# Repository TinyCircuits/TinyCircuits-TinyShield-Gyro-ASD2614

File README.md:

# TinyCircuits TinyShield Gyro Board
# ASD2614 Rev1

These design files are located under design_files/ for the TinyCircuits ASD2614 Rev 1 PCB.  This is a TinyShield board (Square Version, 20mm x 20mm, or Circular 20mm diameter) that has a ST L3G4200D Gyroscope, local power supply and level shifters to connect between the TinyDuino and the accelerometer. 

Format is in Cadsoft Eagle format - Eagle version 6.2 was used for the original design.

For more infomation on this, check out the product page at TinyCircuits.com:  https://tinycircuits.com/collections/sensors/products/gyroscope-tinyshield

#License:

Design by TinyCircuits.
All design files are released under the Creative Commons Attribution Share-Alike 3.0 License, see the following link for details: http://creativecommons.org/licenses/by-sa/3.0

All text above must be included in any redistribution or derived design

This project uses designs and concepts developed as part of the Arduino project and the LilyPad project.  The TinyCircuits design files themselves (schematics, PCB and libraries) are not directly derived from these works' design files and have been created new, however the concepts and basic architecture behind the TinyDuino and TinyLily products are derived and we thank the hard work of the organizations below for their contributions to open-source hardware:
  
Original Arduino Uno Design by Team Arduino

LilyPad Arduino Design by Leah Buechley and Sparkfun Electronics

Please support the open-source hardware community

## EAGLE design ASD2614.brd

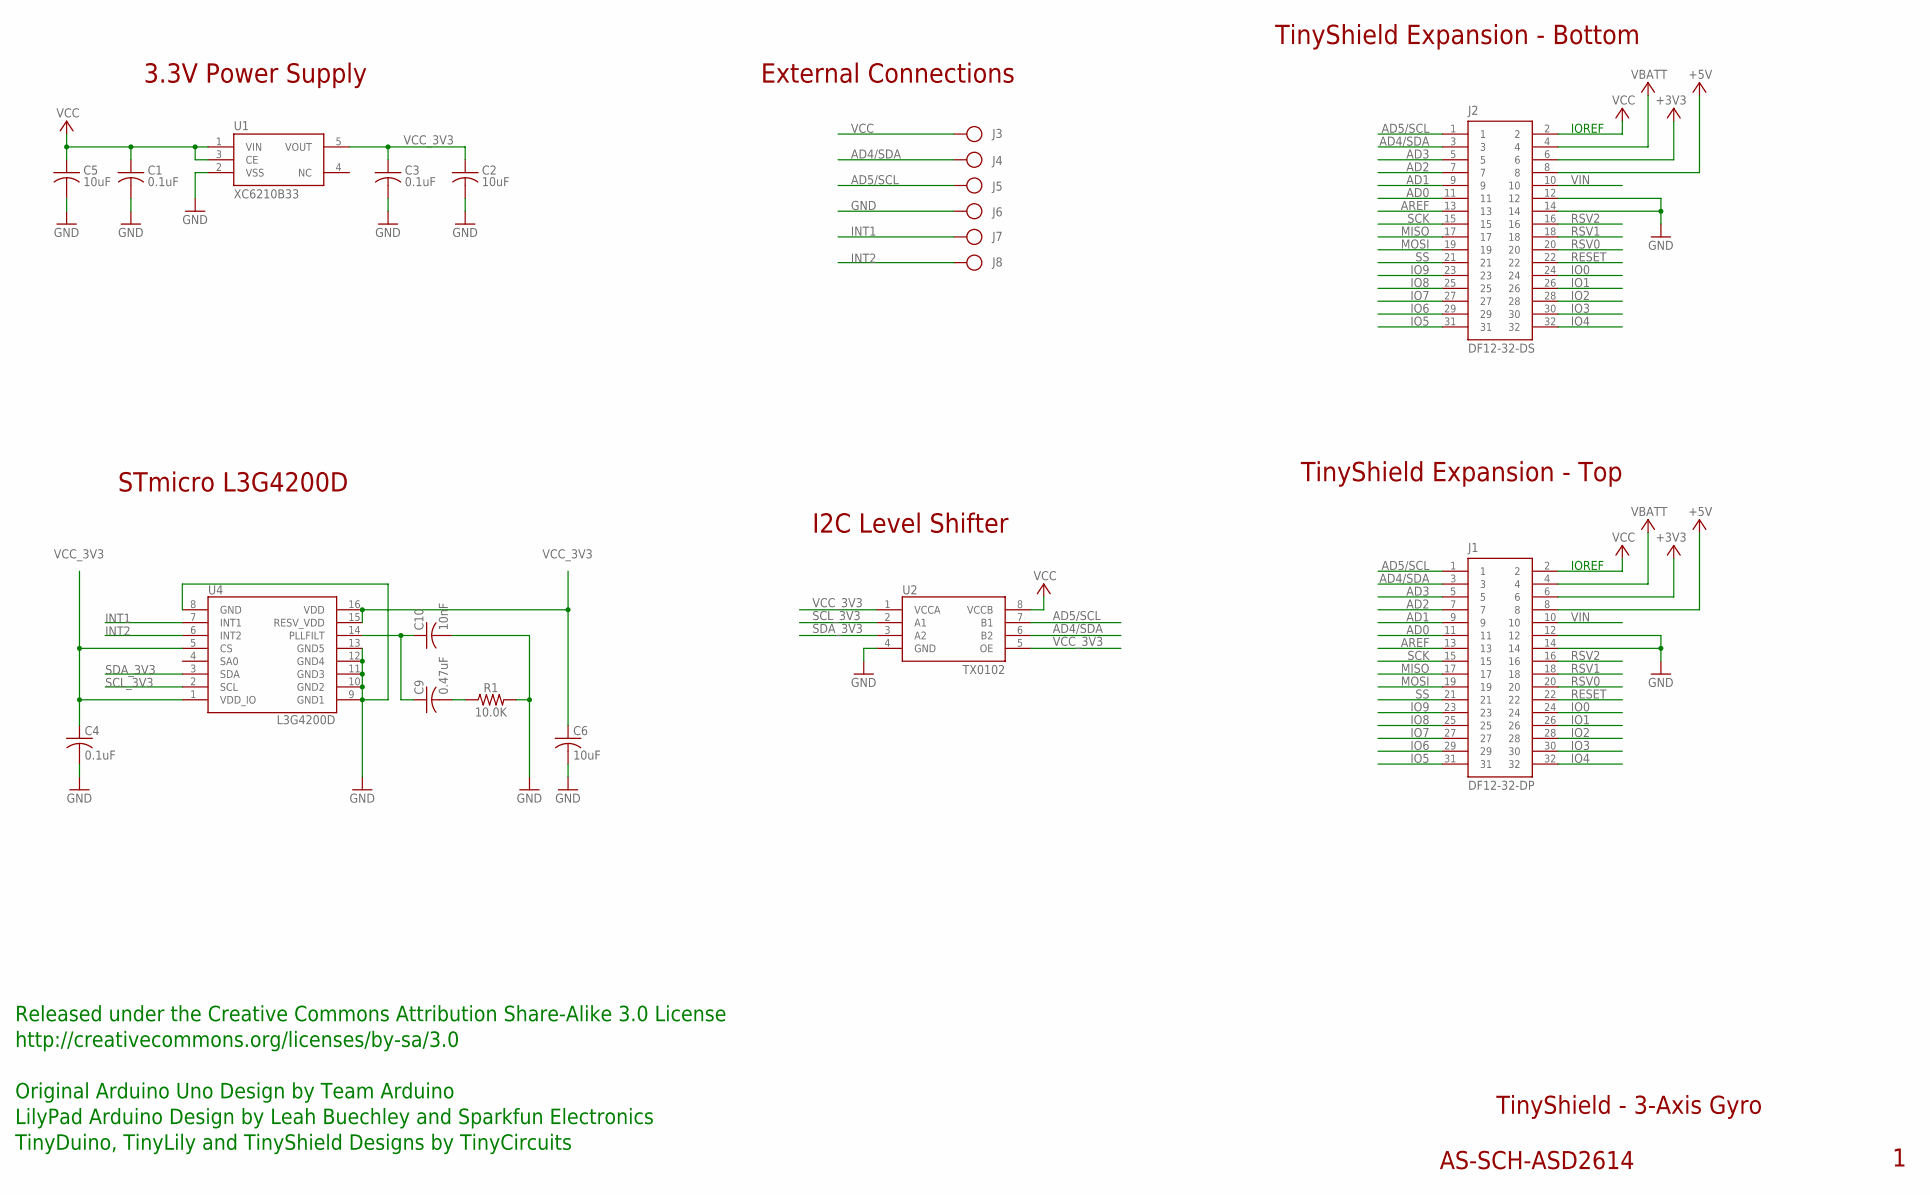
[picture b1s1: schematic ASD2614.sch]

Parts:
C1, C3: 0.1uF; C0402; PARTNO AS-ITM-00008
C2: 10uF; C0805; PARTNO AS-ITM-00045
C4: 0.1uF; C0402
C5: 10uF; C0805
C6: 10uF; C0603
C9: 0.47uF; C0402
C10: 10nF; 0402
J1: DF12-32-DP; PARTNO AS-ITM-00015
J2: DF12-32-DS; PARTNO AS-ITM-00012
J3, J4, J5, J6, J7, J8: PIN_1X.1"; 1X.1"
R1: 10.0K; 0402
U1: XC6210B33; SOT-25
U2: TX0102; DQE(R-PX2SON-N8)
U4: L3G4200D

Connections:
+3V3: J1.6, J2.6
+5V: J1.8, J2.8
AD0: J1.11, J2.11
AD1: J1.9, J2.9
AD2: J1.7, J2.7
AD3: J1.5, J2.5
AD4/SDA: J1.3, J2.3, J4.1, U2.6 (B2)
AD5/SCL: J1.1, J2.1, J5.1, U2.7 (B1)
AREF: J1.13, J2.13
GND: C1.2, C2.2, C3.2, C4.2, C5.2, C6.2, C10.2, J1.12, J1.14, J2.12, J2.14, J6.1, R1.2, U1.2 (VSS), U2.4 (GND), U4.8 (GND), U4.9 (GND1), U4.10 (GND2), U4.11 (GND3), U4.12 (GND4), U4.13 (GND5)
INT1: J7.1, U4.7 (INT1)
INT2: J8.1, U4.6 (INT2)
IO0: J1.24, J2.24
IO1: J1.26, J2.26
IO2: J1.28, J2.28
IO3: J1.30, J2.30
IO4: J1.32, J2.32
IO5: J1.31, J2.31
IO6: J1.29, J2.29
IO7: J1.27, J2.27
IO8: J1.25, J2.25
IO9: J1.23, J2.23
MISO: J1.17, J2.17
MOSI: J1.19, J2.19
unnamed: C9.2, R1.1
unnamed: C9.1, C10.1, U4.14 (PLLFILT)
RESET: J1.22, J2.22
RSV0: J1.20, J2.20
RSV1: J1.18, J2.18
RSV2: J1.16, J2.16
SCK: J1.15, J2.15
SCL_3V3: U2.2 (A1), U4.2 (SCL)
SDA_3V3: U2.3 (A2), U4.3 (SDA)
SS: J1.21, J2.21
VBATT: J1.4, J2.4
VCC: C1.1, C5.1, J1.2, J2.2, J3.1, U1.1 (VIN), U1.3 (CE), U2.8 (VCCB)
VCC_3V3: C2.1, C3.1, C4.1, C6.1, U1.5 (VOUT), U2.1 (VCCA), U2.5 (OE), U4.1 (VDD_IO), U4.5 (CS), U4.15 (RESV_VDD), U4.16 (VDD)
VIN: J1.10, J2.10

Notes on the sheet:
TinyShield Expansion - Bottom
TinyShield - 3-Axis Gyro
AS-SCH-ASD2614
TinyShield Expansion - Top
IOREF
Released under the Creative Commons Attribution Share-Alike 3.0 License
http://creativecommons.org/licenses/by-sa/3.0
LilyPad Arduino Design by Leah Buechley and Sparkfun Electronics
TinyDuino, TinyLily and TinyShield Designs by TinyCircuits
Original Arduino Uno Design by Team Arduino
External Connections
3.3V Power Supply
I2C Level Shifter
STmicro L3G4200D

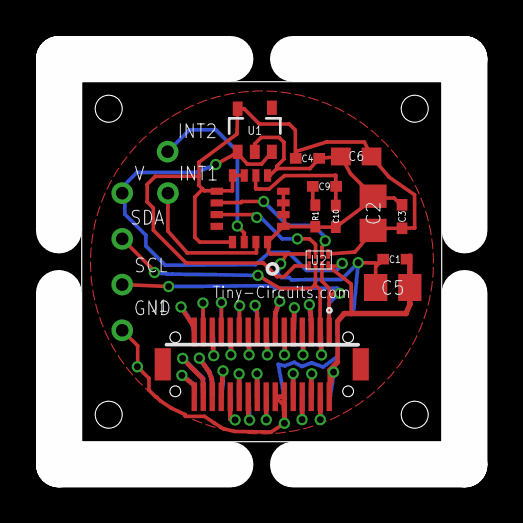
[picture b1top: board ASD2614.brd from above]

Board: 2 copper layers, 20.0 x 20.0 mm, 21 parts (1 on the bottom side), 38 nets.

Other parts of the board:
U$1: DOCFIELD-TINYCIRCUITS-PCB

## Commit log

2014-08-24 Updated Link
2019-01-02 update format
